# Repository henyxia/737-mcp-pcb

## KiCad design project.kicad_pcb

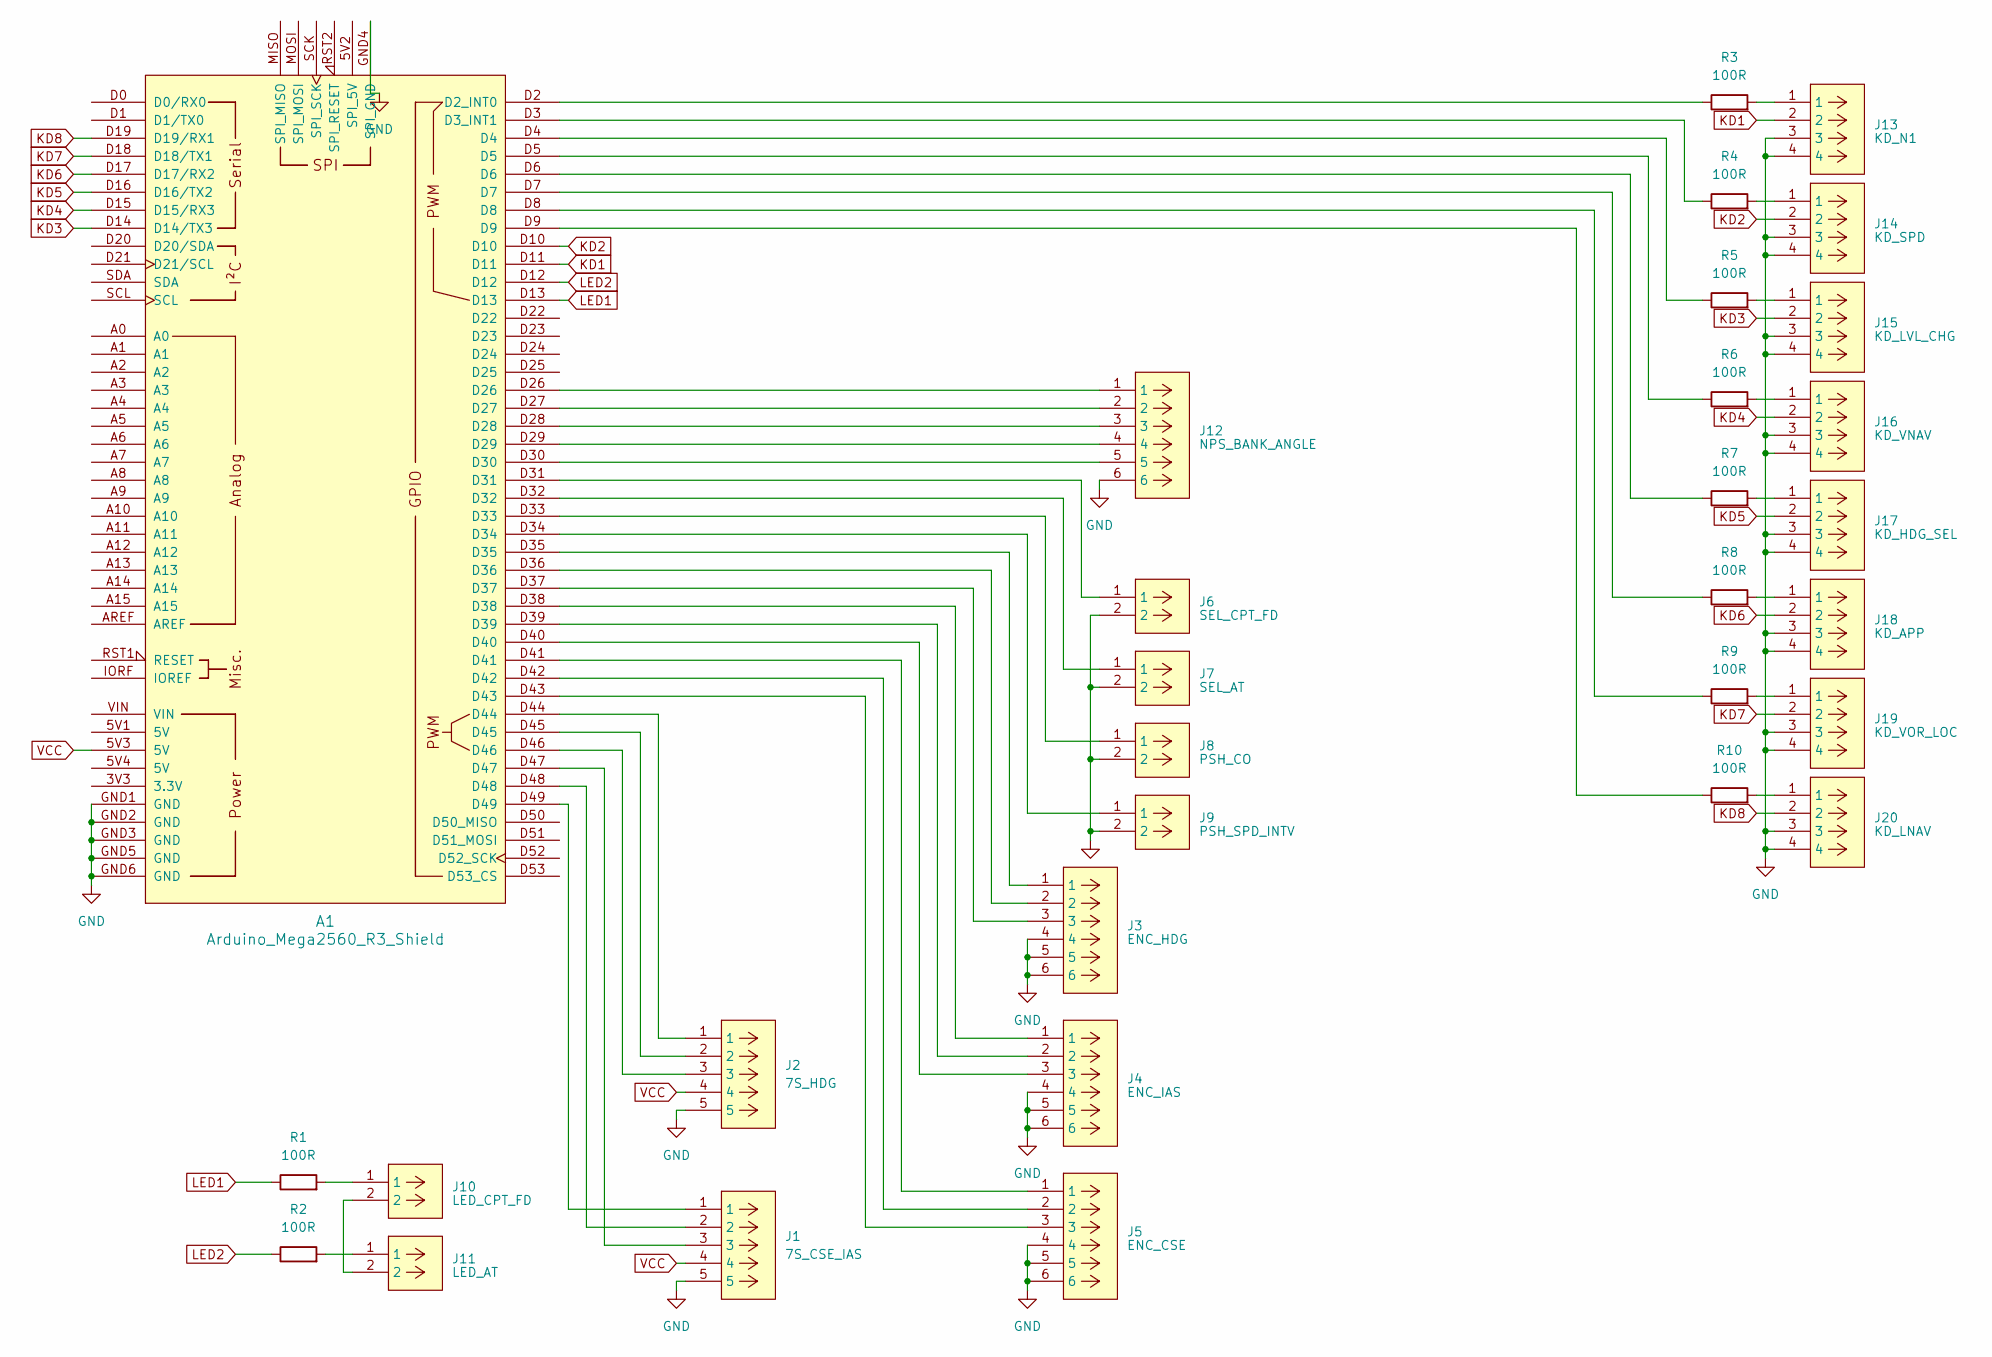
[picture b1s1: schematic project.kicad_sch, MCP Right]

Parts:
A1: Arduino_Mega2560_R3_Shield
J1: 7S_CSE_IAS; TE Conn - 640456-5
J2: 7S_HDG; TE Conn - 640456-5
J3: ENC_HDG; TE Conn - 640456-6
J4: ENC_IAS; TE Conn - 640456-6
J5: ENC_CSE; TE Conn - 640456-6
J6: SEL_CPT_FD; TE Conn - 640456-2
J7: SEL_AT; TE Conn - 640456-2
J8: PSH_CO; TE Conn - 640456-2
J9: PSH_SPD_INTV; TE Conn - 640456-2
J10: LED_CPT_FD; TE Conn - 640456-2
J11: LED_AT; TE Conn - 640456-2
J12: NPS_BANK_ANGLE; TE Conn - 640456-6
J13: KD_N1; TE Conn - 640456-4
J14: KD_SPD; TE Conn - 640456-4
J15: KD_LVL_CHG; TE Conn - 640456-4
J16: KD_VNAV; TE Conn - 640456-4
J17: KD_HDG_SEL; TE Conn - 640456-4
J18: KD_APP; TE Conn - 640456-4
J19: KD_VOR_LOC; TE Conn - 640456-4
J20: KD_LNAV; TE Conn - 640456-4
R1, R2, R3, R4, R5, R6, R7, R8, R9, R10: 100R; xs resistor PT

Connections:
GND: A1.GND1 (GND), A1.GND2 (GND), A1.GND3 (GND), A1.GND4 (SPI_GND), A1.GND5 (GND), A1.GND6 (GND), J1.5, J2.5, J3.4, J3.5, J3.6, J4.4, J4.5, J4.6, J5.4, J5.5, J5.6, J6.2, J7.2, J8.2, J9.2, J12.6, J13.3, J13.4, J14.3, J14.4, J15.3, J15.4, J16.3, J16.4, J17.3, J17.4, J18.3, J18.4, J19.3, J19.4, J20.3, J20.4
KD1: A1.D11, J13.2
KD2: A1.D10, J14.2
KD3: A1.D14 (D14/TX3), J15.2
KD4: A1.D15 (D15/RX3), J16.2
KD5: A1.D16 (D16/TX2), J17.2
KD6: A1.D17 (D17/RX2), J18.2
KD7: A1.D18 (D18/TX1), J19.2
KD8: A1.D19 (D19/RX1), J20.2
LED1: A1.D13, R1.1
LED2: A1.D12, R2.1
unnamed: A1.D2 (D2_INT0), R3.1
unnamed: A1.D3 (D3_INT1), R4.1
unnamed: A1.D4, R5.1
unnamed: A1.D5, R6.1
unnamed: A1.D6, R7.1
unnamed: A1.D7, R8.1
unnamed: A1.D8, R9.1
unnamed: A1.D9, R10.1
unnamed: A1.D26, J12.1
unnamed: A1.D27, J12.2
unnamed: A1.D28, J12.3
unnamed: A1.D29, J12.4
unnamed: A1.D30, J12.5
unnamed: A1.D31, J6.1
unnamed: A1.D32, J7.1
unnamed: A1.D33, J8.1
unnamed: A1.D34, J9.1
unnamed: A1.D35, J3.1
unnamed: A1.D36, J3.2
unnamed: A1.D37, J3.3
unnamed: A1.D38, J4.1
unnamed: A1.D39, J4.2
unnamed: A1.D40, J4.3
unnamed: A1.D41, J5.1
unnamed: A1.D42, J5.2
unnamed: A1.D43, J5.3
unnamed: A1.D44, J2.1
unnamed: A1.D45, J2.2
unnamed: A1.D46, J2.3
unnamed: A1.D47, J1.3
unnamed: A1.D48, J1.2
unnamed: A1.D49, J1.1
unnamed: J10.1, R1.2
unnamed: J10.2, J11.2
unnamed: J11.1, R2.2
unnamed: J13.1, R3.2
unnamed: J14.1, R4.2
unnamed: J15.1, R5.2
unnamed: J16.1, R6.2
unnamed: J17.1, R7.2
unnamed: J18.1, R8.2
unnamed: J19.1, R9.2
unnamed: J20.1, R10.2
VCC: A1.5V3 (5V), J1.4, J2.4

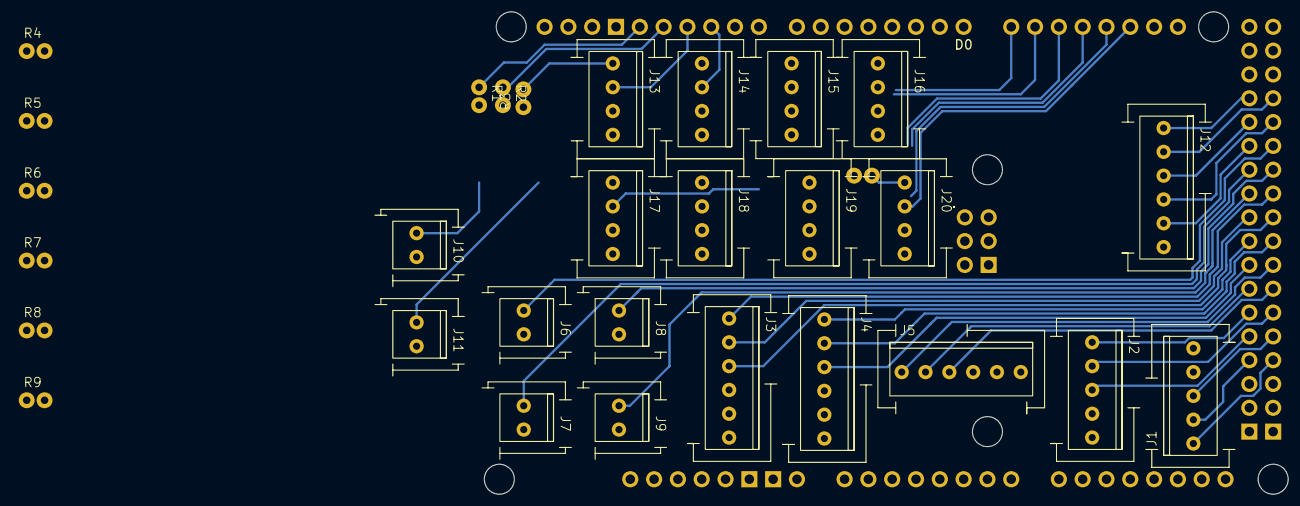
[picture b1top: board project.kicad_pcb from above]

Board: 2 copper layers, 31 parts (0 on the bottom side), 55 nets.

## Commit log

2024-02-13 doc: add basic readme
2024-03-03 feat(schematic): add right mcp
2024-03-04 feat: route south part of bottom layer
